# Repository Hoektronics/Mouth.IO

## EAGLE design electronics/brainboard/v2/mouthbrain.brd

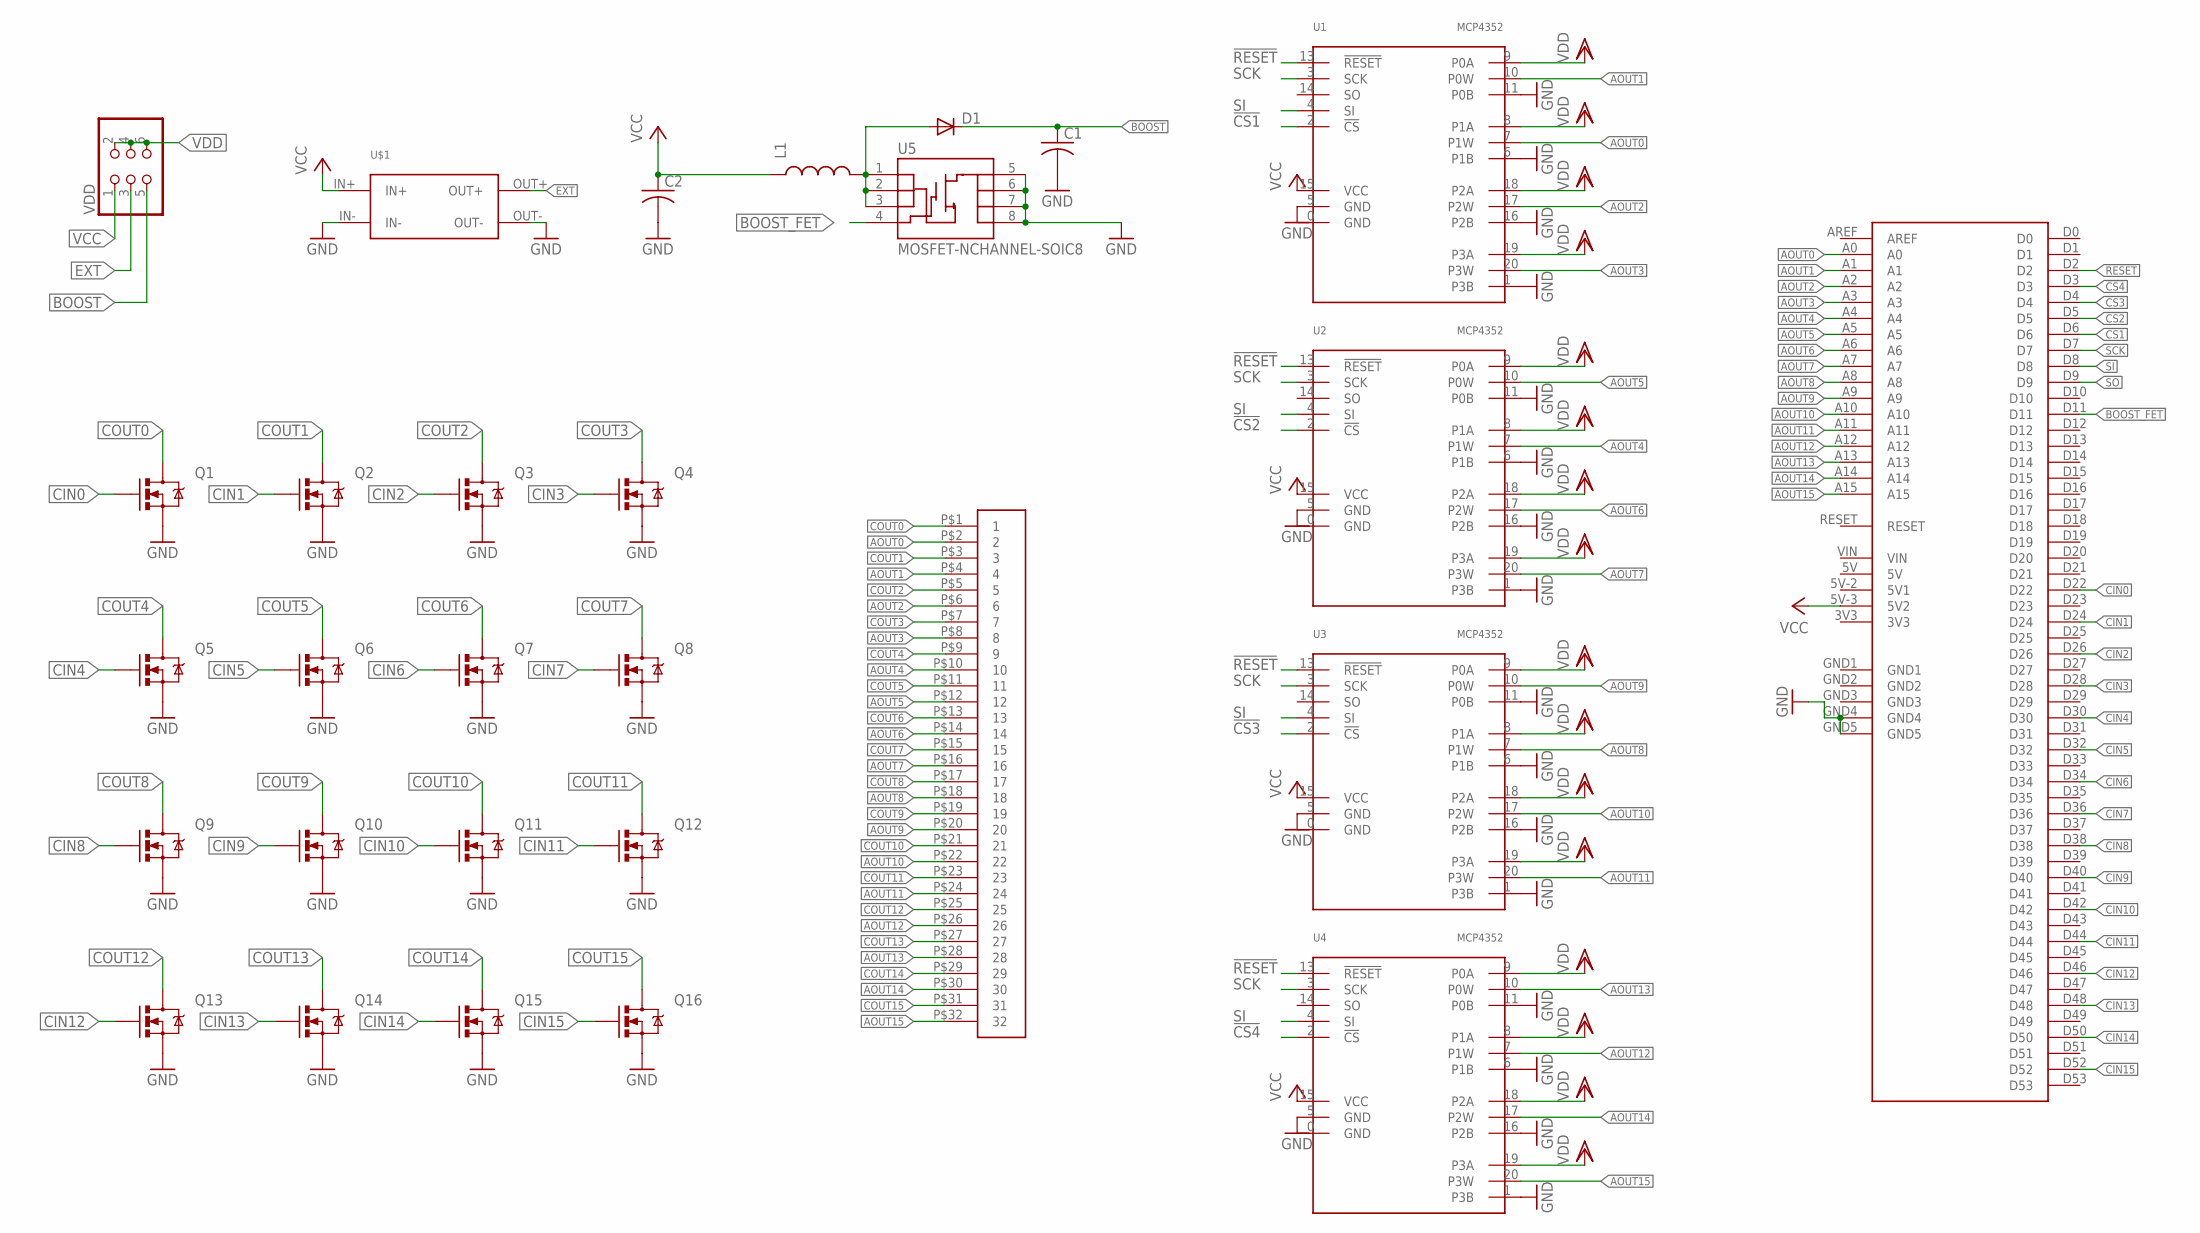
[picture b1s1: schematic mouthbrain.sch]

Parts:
C1, C2: C-USC1206; C1206
D1: DIODESMA; SMA-DIODE
L1: INDUCTOR1206H*; INDUCTOR-1206
Q1, Q2, Q3, Q4, Q5, Q6, Q7, Q8, Q9, Q10, Q11, Q12, Q13, Q14, Q15, Q16: MOSFET-NCHANNELSMD; SOT23-3
U1, U2, U3, U4: MCP4352; QFN-20-PAD
U5: MOSFET-NCHANNEL-SOIC8; SO08
U$1: DC-DC-CONVERTER; DC-DC-MODULE
U$2: FPC-0.5-32HORIZ; FPC-32-HORIZONTAL
U$3: ARDUINO-MEGA
VDD: PINHD-2X3; 2X03

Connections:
!CS1: U1.2 (!CS), U$3.D6
!CS2: U2.2 (!CS), U$3.D5
!CS3: U3.2 (!CS), U$3.D4
!CS4: U4.2 (!CS), U$3.D3
!RESET: U1.13 (!RESET), U2.13 (!RESET), U3.13 (!RESET), U4.13 (!RESET), U$3.D2
AOUT0: U1.7 (P1W), U$2.P$2 (2), U$3.A0
AOUT1: U1.10 (P0W), U$2.P$4 (4), U$3.A1
AOUT2: U1.17 (P2W), U$2.P$6 (6), U$3.A2
AOUT3: U1.20 (P3W), U$2.P$8 (8), U$3.A3
AOUT4: U2.7 (P1W), U$2.P$10 (10), U$3.A4
AOUT5: U2.10 (P0W), U$2.P$12 (12), U$3.A5
AOUT6: U2.17 (P2W), U$2.P$14 (14), U$3.A6
AOUT7: U2.20 (P3W), U$2.P$16 (16), U$3.A7
AOUT8: U3.7 (P1W), U$2.P$18 (18), U$3.A8
AOUT9: U3.10 (P0W), U$2.P$20 (20), U$3.A9
AOUT10: U3.17 (P2W), U$2.P$22 (22), U$3.A10
AOUT11: U3.20 (P3W), U$2.P$24 (24), U$3.A11
AOUT12: U4.7 (P1W), U$2.P$26 (26), U$3.A12
AOUT13: U4.10 (P0W), U$2.P$28 (28), U$3.A13
AOUT14: U4.17 (P2W), U$2.P$30 (30), U$3.A14
AOUT15: U4.20 (P3W), U$2.P$32 (32), U$3.A15
BOOST: C1.1, D1.C, VDD.5
BOOST_FET: U5.4 (G), U$3.D11
CIN0: Q1.1 (G), U$3.D22
CIN1: Q2.1 (G), U$3.D24
CIN2: Q3.1 (G), U$3.D26
CIN3: Q4.1 (G), U$3.D28
CIN4: Q5.1 (G), U$3.D30
CIN5: Q6.1 (G), U$3.D32
CIN6: Q7.1 (G), U$3.D34
CIN7: Q8.1 (G), U$3.D36
CIN8: Q9.1 (G), U$3.D38
CIN9: Q10.1 (G), U$3.D40
CIN10: Q11.1 (G), U$3.D42
CIN11: Q12.1 (G), U$3.D44
CIN12: Q13.1 (G), U$3.D46
CIN13: Q14.1 (G), U$3.D48
CIN14: Q15.1 (G), U$3.D50
CIN15: Q16.1 (G), U$3.D52
COUT0: Q1.3 (D), U$2.P$1 (1)
COUT1: Q2.3 (D), U$2.P$3 (3)
COUT2: Q3.3 (D), U$2.P$5 (5)
COUT3: Q4.3 (D), U$2.P$7 (7)
COUT4: Q5.3 (D), U$2.P$9 (9)
COUT5: Q6.3 (D), U$2.P$11 (11)
COUT6: Q7.3 (D), U$2.P$13 (13)
COUT7: Q8.3 (D), U$2.P$15 (15)
COUT8: Q9.3 (D), U$2.P$17 (17)
COUT9: Q10.3 (D), U$2.P$19 (19)
COUT10: Q11.3 (D), U$2.P$21 (21)
COUT11: Q12.3 (D), U$2.P$23 (23)
COUT12: Q13.3 (D), U$2.P$25 (25)
COUT13: Q14.3 (D), U$2.P$27 (27)
COUT14: Q15.3 (D), U$2.P$29 (29)
COUT15: Q16.3 (D), U$2.P$31 (31)
EXT: U$1.OUT+, VDD.3
GND: C1.2, C2.2, Q1.2 (S), Q2.2 (S), Q3.2 (S), Q4.2 (S), Q5.2 (S), Q6.2 (S), Q7.2 (S), Q8.2 (S), Q9.2 (S), Q10.2 (S), Q11.2 (S), Q12.2 (S), Q13.2 (S), Q14.2 (S), Q15.2 (S), Q16.2 (S), U1.0 (GND), U1.1 (P3B), U1.5 (GND), U1.6 (P1B), U1.11 (P0B), U1.16 (P2B), U2.0 (GND), U2.1 (P3B), U2.5 (GND), U2.6 (P1B), U2.11 (P0B), U2.16 (P2B), U3.0 (GND), U3.1 (P3B), U3.5 (GND), U3.6 (P1B), U3.11 (P0B), U3.16 (P2B), U4.0 (GND), U4.1 (P3B), U4.5 (GND), U4.6 (P1B), U4.11 (P0B), U4.16 (P2B), U5.5 (D), U5.6 (D), U5.7 (D), U5.8 (D), U$1.IN-, U$1.OUT-, U$3.GND4, U$3.GND5
unnamed: D1.A, L1.P$2 (2), U5.1 (S), U5.2 (S), U5.3 (S)
SCK: U1.3 (SCK), U2.3 (SCK), U3.3 (SCK), U4.3 (SCK), U$3.D7
SI: U1.4 (SI), U2.4 (SI), U3.4 (SI), U4.4 (SI), U$3.D8
SO: U$3.D9
VCC: C2.1, L1.P$1 (1), U1.15 (VCC), U2.15 (VCC), U3.15 (VCC), U4.15 (VCC), U$1.IN+, U$3.5V-3 (5V2), VDD.1
VDD: U1.8 (P1A), U1.9 (P0A), U1.18 (P2A), U1.19 (P3A), U2.8 (P1A), U2.9 (P0A), U2.18 (P2A), U2.19 (P3A), U3.8 (P1A), U3.9 (P0A), U3.18 (P2A), U3.19 (P3A), U4.8 (P1A), U4.9 (P0A), U4.18 (P2A), U4.19 (P3A), VDD.2, VDD.4, VDD.6

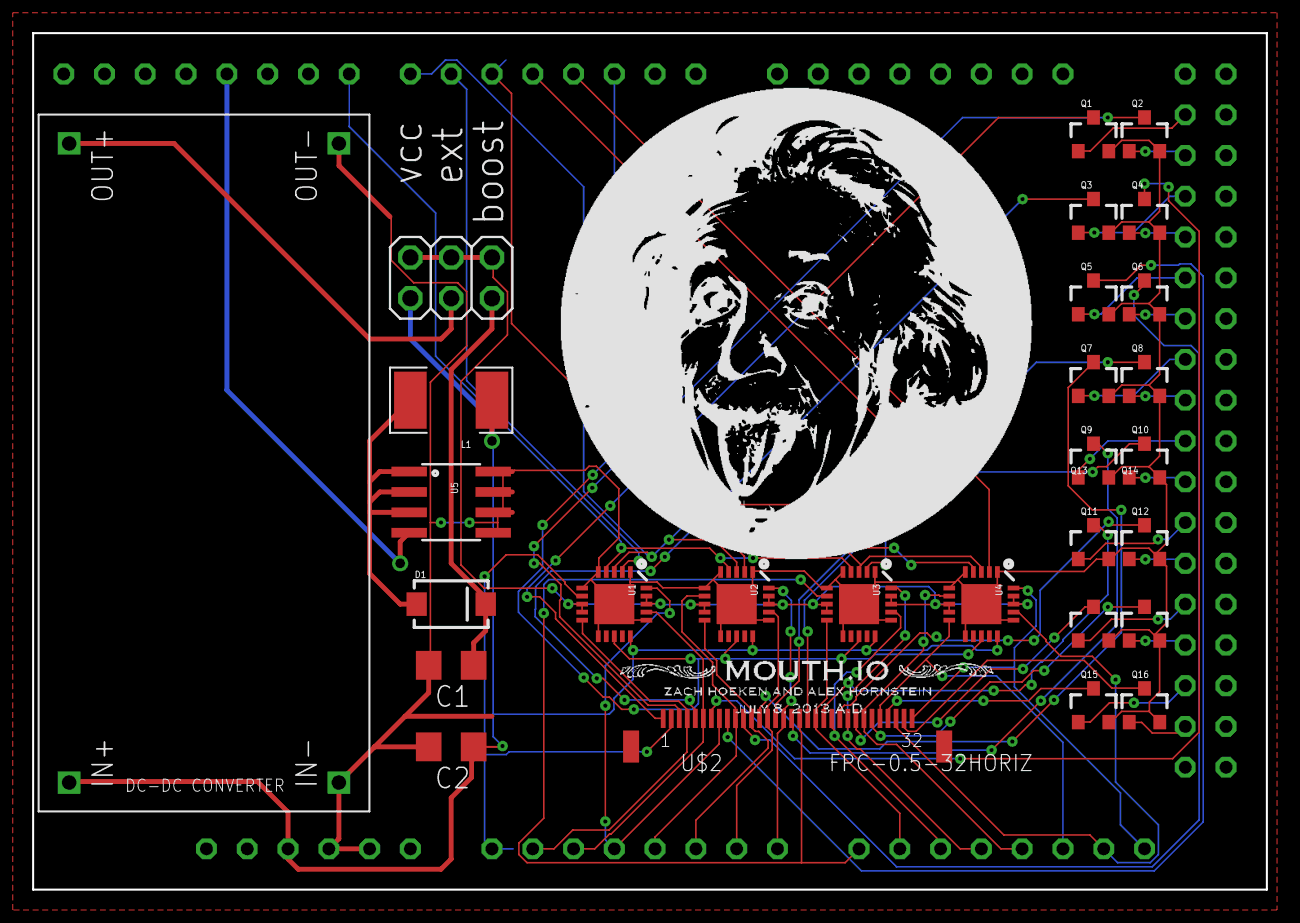
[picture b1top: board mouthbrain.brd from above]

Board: 2 copper layers, 76.8 x 53.3 mm, 29 parts (0 on the bottom side), 62 nets.

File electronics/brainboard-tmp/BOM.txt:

Partlist

Exported from mouthbrain.brd at 8/7/13 3:34 PM

EAGLE Version 6.4.1 Copyright (c) 1988-2013 CadSoft

Assembly variant: 

Part     Value                 Package       Library     Position (mil)        Orientation

C1                             C1206         rcl         (3050 1700)           R270
C2                             C1206         rcl         (3250 1700)           R270
D1                             SMA-DIODE     SparkFun    (2900 1700)           R90
L1                             INDUCTOR-1206 SparkFun    (2400 1700)           R270
MEGA     ARDUINO-MEGAFULL      ARDUINO_MEGA  SparkFun    (0 100)               R0
Q1       MOSFET-NCHANNELSMD    SOT23-3       SparkFun    (2350 900)            R90
Q2       MOSFET-NCHANNELSMD    SOT23-3       SparkFun    (2350 1050)           R90
Q3       MOSFET-NCHANNELSMD    SOT23-3       SparkFun    (2350 1200)           R90
Q4       MOSFET-NCHANNELSMD    SOT23-3       SparkFun    (2350 1350)           R90
Q5       MOSFET-NCHANNELSMD    SOT23-3       SparkFun    (2500 900)            R90
Q6       MOSFET-NCHANNELSMD    SOT23-3       SparkFun    (2500 1050)           R90
Q7       MOSFET-NCHANNELSMD    SOT23-3       SparkFun    (2500 1200)           R90
Q8       MOSFET-NCHANNELSMD    SOT23-3       SparkFun    (2500 1350)           R90
Q9       MOSFET-NCHANNELSMD    SOT23-3       SparkFun    (2650 900)            R90
Q10      MOSFET-NCHANNELSMD    SOT23-3       SparkFun    (2650 1050)           R90
Q11      MOSFET-NCHANNELSMD    SOT23-3       SparkFun    (2650 1200)           R90
Q12      MOSFET-NCHANNELSMD    SOT23-3       SparkFun    (2650 1350)           R90
Q13      MOSFET-NCHANNELSMD    SOT23-3       SparkFun    (2800 900)            R90
Q14      MOSFET-NCHANNELSMD    SOT23-3       SparkFun    (2800 1050)           R90
Q15      MOSFET-NCHANNELSMD    SOT23-3       SparkFun    (2800 1200)           R90
Q16      MOSFET-NCHANNELSMD    SOT23-3       SparkFun    (2800 1350)           R90
U$1      DC-DC-CONVERTER       DC-DC-MODULE  Hoektronics (1294 1146)           R90
U$2      FPC-0.5-32            FPC-PCB-32    Hoektronics (2750 675)            R0
U1       MCP4352               QFN-20        mouthbrain  (3000 1000)           R90
U2       MCP4352               QFN-20        mouthbrain  (3000 1350)           R90
U3       MCP4352               QFN-20        mouthbrain  (3250 1000)           R90
U4       MCP4352               QFN-20        mouthbrain  (3250 1350)           R90
U5       MOSFET-NCHANNEL-SOIC8 SO08          SparkFun    (2650 1700)           R0
VDD                            2X03          pinhead     (2100 1700)           R90

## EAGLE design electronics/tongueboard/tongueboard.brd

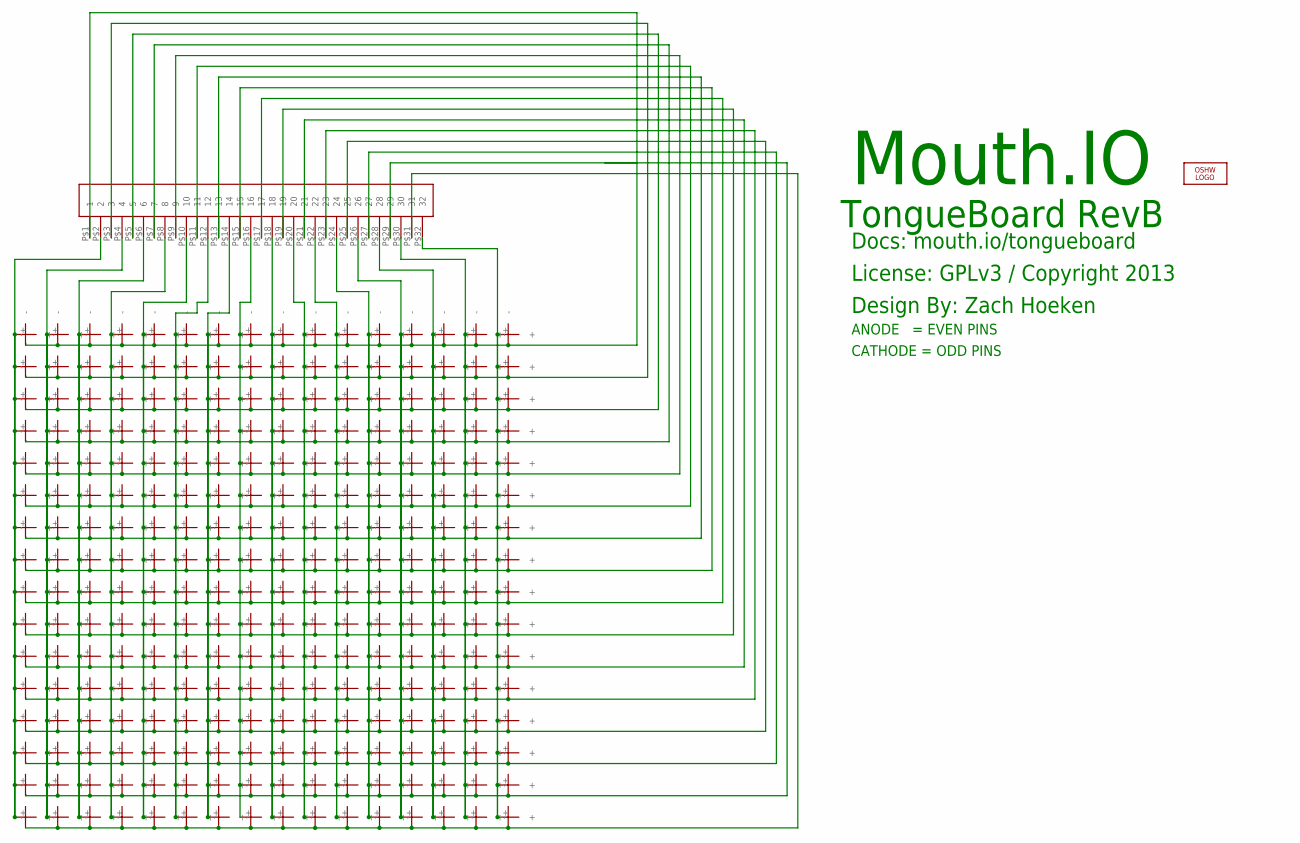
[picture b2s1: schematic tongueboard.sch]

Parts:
LOGO1: OSHW_LOGO_10MIL; OSHW_10X500_NOTEXT_COPPER
U$1, U$2, U$3, U$4, U$5, U$6, U$7, U$8, U$9, U$10, U$11, U$12, U$13, U$14, U$15, U$17, U$18, U$19, U$20, U$21, U$22, U$23, U$24, U$25, U$26, U$27, U$28, U$29, U$30, U$32, U$33, U$34, U$35, U$36, U$37, U$38, U$39, U$40, U$41, U$42, U$43, U$44, U$45, U$47, U$48, U$49, U$50, U$51, U$52, U$53, U$54, U$55, U$56, U$57, U$58, U$59, U$60, U$62, U$63, U$64, U$65, U$66, U$67, U$68, U$69, U$70, U$71, U$72, U$73, U$74, U$75, U$77, U$78, U$79, U$80, U$81, U$82, U$83, U$84, U$85, U$86, U$87, U$88, U$89, U$90, U$92, U$93, U$94, U$95, U$96, U$97, U$98, U$99, U$100, U$101, U$102, U$103, U$104, U$105, U$107, U$108, U$109, U$110, U$111, U$112, U$113, U$114, U$115, U$116, U$117, U$118, U$119, U$120, U$122, U$123, U$124, U$125, U$126, U$127, U$128, U$129, U$130, U$131, U$132, U$133, U$134, U$135, U$137, U$138, U$139, U$140, U$141, U$142, U$143, U$144, U$145, U$146, U$147, U$148, U$149, U$150, U$152, U$153, U$154, U$155, U$156, U$157, U$158, U$159, U$160, U$161, U$162, U$163, U$164, U$165, U$167, U$168, U$169, U$170, U$171, U$172, U$173, U$174, U$175, U$176, U$177, U$178, U$179, U$180, U$182, U$183, U$184, U$185, U$186, U$187, U$188, U$189, U$190, U$191, U$192, U$193, U$194, U$195, U$197, U$198, U$199, U$200, U$201, U$202, U$203, U$204, U$205, U$206, U$207, U$208, U$209, U$210, U$212, U$213, U$214, U$215, U$216, U$217, U$218, U$219, U$220, U$221, U$222, U$223, U$224, U$225, U$227, U$228, U$229, U$230, U$231, U$232, U$233, U$234, U$235, U$236, U$237, U$238, U$239, U$240, U$242, U$243, U$244, U$245, U$246, U$247, U$248, U$249, U$250, U$251, U$252, U$253, U$254, U$255, U$256: ELECTRODE60MIL; 61MIL
U$16, U$31, U$46, U$61, U$76, U$91, U$106, U$121, U$136, U$151, U$166, U$181, U$196, U$211, U$226, U$241: ELECTRODE61MILJCT; 61MILJCT
U$257: FPC-0.5-32; FPC-32-WIRE

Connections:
A0: U$1.+, U$17.+, U$33.+, U$49.+, U$65.+, U$81.+, U$97.+, U$113.+, U$129.+, U$145.+, U$161.+, U$177.+, U$193.+, U$209.+, U$225.+, U$241.+, U$257.P$2 (2)
A1: U$2.+, U$18.+, U$34.+, U$50.+, U$66.+, U$82.+, U$98.+, U$114.+, U$130.+, U$146.+, U$162.+, U$178.+, U$194.+, U$210.+, U$226.+, U$242.+, U$257.P$4 (4)
A2: U$3.+, U$19.+, U$35.+, U$51.+, U$67.+, U$83.+, U$99.+, U$115.+, U$131.+, U$147.+, U$163.+, U$179.+, U$195.+, U$211.+, U$227.+, U$243.+, U$257.P$6 (6)
A3: U$4.+, U$20.+, U$36.+, U$52.+, U$68.+, U$84.+, U$100.+, U$116.+, U$132.+, U$148.+, U$164.+, U$180.+, U$196.+, U$212.+, U$228.+, U$244.+, U$257.P$8 (8)
A4: U$5.+, U$21.+, U$37.+, U$53.+, U$69.+, U$85.+, U$101.+, U$117.+, U$133.+, U$149.+, U$165.+, U$181.+, U$197.+, U$213.+, U$229.+, U$245.+, U$257.P$10 (10)
A5: U$6.+, U$22.+, U$38.+, U$54.+, U$70.+, U$86.+, U$102.+, U$118.+, U$134.+, U$150.+, U$166.+, U$182.+, U$198.+, U$214.+, U$230.+, U$246.+, U$257.P$12 (12)
A6: U$7.+, U$23.+, U$39.+, U$55.+, U$71.+, U$87.+, U$103.+, U$119.+, U$135.+, U$151.+, U$167.+, U$183.+, U$199.+, U$215.+, U$231.+, U$247.+, U$257.P$14 (14)
A7: U$8.+, U$24.+, U$40.+, U$56.+, U$72.+, U$88.+, U$104.+, U$120.+, U$136.+, U$152.+, U$168.+, U$184.+, U$200.+, U$216.+, U$232.+, U$248.+, U$257.P$16 (16)
A8: U$9.+, U$25.+, U$41.+, U$57.+, U$73.+, U$89.+, U$105.+, U$121.+, U$137.+, U$153.+, U$169.+, U$185.+, U$201.+, U$217.+, U$233.+, U$249.+, U$257.P$18 (18)
A9: U$10.+, U$26.+, U$42.+, U$58.+, U$74.+, U$90.+, U$106.+, U$122.+, U$138.+, U$154.+, U$170.+, U$186.+, U$202.+, U$218.+, U$234.+, U$250.+, U$257.P$20 (20)
A10: U$11.+, U$27.+, U$43.+, U$59.+, U$75.+, U$91.+, U$107.+, U$123.+, U$139.+, U$155.+, U$171.+, U$187.+, U$203.+, U$219.+, U$235.+, U$251.+, U$257.P$22 (22)
A11: U$12.+, U$28.+, U$44.+, U$60.+, U$76.+, U$92.+, U$108.+, U$124.+, U$140.+, U$156.+, U$172.+, U$188.+, U$204.+, U$220.+, U$236.+, U$252.+, U$257.P$24 (24)
A12: U$13.+, U$29.+, U$45.+, U$61.+, U$77.+, U$93.+, U$109.+, U$125.+, U$141.+, U$157.+, U$173.+, U$189.+, U$205.+, U$221.+, U$237.+, U$253.+, U$257.P$26 (26)
A13: U$14.+, U$30.+, U$46.+, U$62.+, U$78.+, U$94.+, U$110.+, U$126.+, U$142.+, U$158.+, U$174.+, U$190.+, U$206.+, U$222.+, U$238.+, U$254.+, U$257.P$28 (28)
A14: U$15.+, U$31.+, U$47.+, U$63.+, U$79.+, U$95.+, U$111.+, U$127.+, U$143.+, U$159.+, U$175.+, U$191.+, U$207.+, U$223.+, U$239.+, U$255.+, U$257.P$30 (30)
A15: U$16.+, U$32.+, U$48.+, U$64.+, U$80.+, U$96.+, U$112.+, U$128.+, U$144.+, U$160.+, U$176.+, U$192.+, U$208.+, U$224.+, U$240.+, U$256.+, U$257.P$32 (32)
C0: U$241.-, U$242.-, U$243.-, U$244.-, U$245.-, U$246.-, U$247.-, U$248.-, U$249.-, U$250.-, U$251.-, U$252.-, U$253.-, U$254.-, U$255.-, U$256.-, U$257.P$1 (1)
C1: U$225.-, U$226.-, U$227.-, U$228.-, U$229.-, U$230.-, U$231.-, U$232.-, U$233.-, U$234.-, U$235.-, U$236.-, U$237.-, U$238.-, U$239.-, U$240.-, U$257.P$3 (3)
C2: U$209.-, U$210.-, U$211.-, U$212.-, U$213.-, U$214.-, U$215.-, U$216.-, U$217.-, U$218.-, U$219.-, U$220.-, U$221.-, U$222.-, U$223.-, U$224.-, U$257.P$5 (5)
C3: U$193.-, U$194.-, U$195.-, U$196.-, U$197.-, U$198.-, U$199.-, U$200.-, U$201.-, U$202.-, U$203.-, U$204.-, U$205.-, U$206.-, U$207.-, U$208.-, U$257.P$7 (7)
C4: U$177.-, U$178.-, U$179.-, U$180.-, U$181.-, U$182.-, U$183.-, U$184.-, U$185.-, U$186.-, U$187.-, U$188.-, U$189.-, U$190.-, U$191.-, U$192.-, U$257.P$9 (9)
C5: U$161.-, U$162.-, U$163.-, U$164.-, U$165.-, U$166.-, U$167.-, U$168.-, U$169.-, U$170.-, U$171.-, U$172.-, U$173.-, U$174.-, U$175.-, U$176.-, U$257.P$11 (11)
C6: U$145.-, U$146.-, U$147.-, U$148.-, U$149.-, U$150.-, U$151.-, U$152.-, U$153.-, U$154.-, U$155.-, U$156.-, U$157.-, U$158.-, U$159.-, U$160.-, U$257.P$13 (13)
C7: U$129.-, U$130.-, U$131.-, U$132.-, U$133.-, U$134.-, U$135.-, U$136.-, U$137.-, U$138.-, U$139.-, U$140.-, U$141.-, U$142.-, U$143.-, U$144.-, U$257.P$15 (15)
C8: U$113.-, U$114.-, U$115.-, U$116.-, U$117.-, U$118.-, U$119.-, U$120.-, U$121.-, U$122.-, U$123.-, U$124.-, U$125.-, U$126.-, U$127.-, U$128.-, U$257.P$17 (17)
C9: U$97.-, U$98.-, U$99.-, U$100.-, U$101.-, U$102.-, U$103.-, U$104.-, U$105.-, U$106.-, U$107.-, U$108.-, U$109.-, U$110.-, U$111.-, U$112.-, U$257.P$19 (19)
C10: U$81.-, U$82.-, U$83.-, U$84.-, U$85.-, U$86.-, U$87.-, U$88.-, U$89.-, U$90.-, U$91.-, U$92.-, U$93.-, U$94.-, U$95.-, U$96.-, U$257.P$21 (21)
C11: U$65.-, U$66.-, U$67.-, U$68.-, U$69.-, U$70.-, U$71.-, U$72.-, U$73.-, U$74.-, U$75.-, U$76.-, U$77.-, U$78.-, U$79.-, U$80.-, U$257.P$23 (23)
C12: U$49.-, U$50.-, U$51.-, U$52.-, U$53.-, U$54.-, U$55.-, U$56.-, U$57.-, U$58.-, U$59.-, U$60.-, U$61.-, U$62.-, U$63.-, U$64.-, U$257.P$25 (25)
C13: U$33.-, U$34.-, U$35.-, U$36.-, U$37.-, U$38.-, U$39.-, U$40.-, U$41.-, U$42.-, U$43.-, U$44.-, U$45.-, U$46.-, U$47.-, U$48.-, U$257.P$27 (27)
C14: U$17.-, U$18.-, U$19.-, U$20.-, U$21.-, U$22.-, U$23.-, U$24.-, U$25.-, U$26.-, U$27.-, U$28.-, U$29.-, U$30.-, U$31.-, U$32.-, U$257.P$29 (29)
C15: U$1.-, U$2.-, U$3.-, U$4.-, U$5.-, U$6.-, U$7.-, U$8.-, U$9.-, U$10.-, U$11.-, U$12.-, U$13.-, U$14.-, U$15.-, U$16.-, U$257.P$31 (31)

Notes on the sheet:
Mouth.IO
TongueBoard RevB
ANODE = EVEN PINS
CATHODE = ODD PINS
Docs: mouth.io/tongueboard
License: GPLv3 / Copyright 2013
Design By: Zach Hoeken

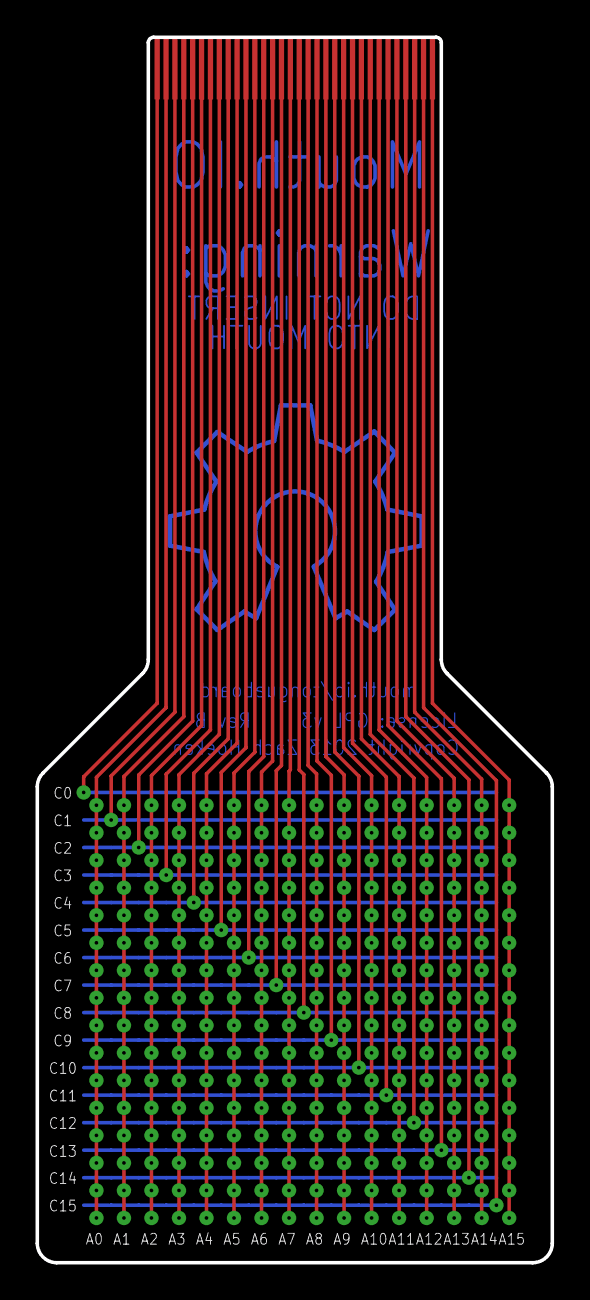
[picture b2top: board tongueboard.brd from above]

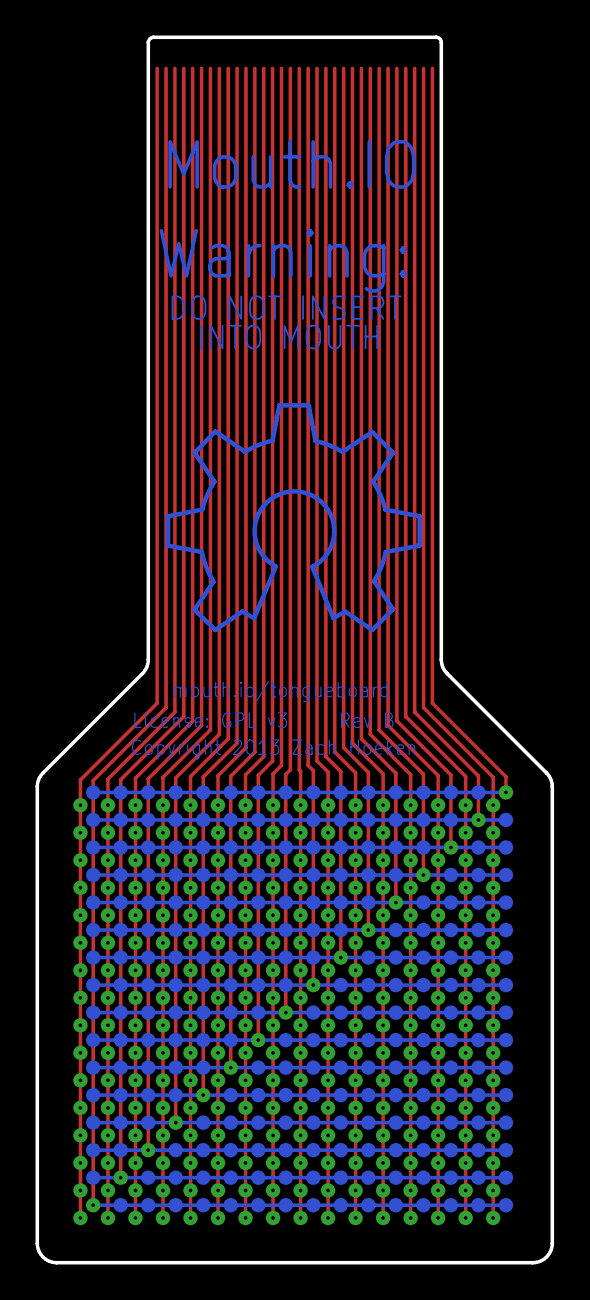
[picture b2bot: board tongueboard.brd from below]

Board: 2 copper layers, 29.0 x 69.0 mm, 258 parts (256 on the bottom side), 32 nets.

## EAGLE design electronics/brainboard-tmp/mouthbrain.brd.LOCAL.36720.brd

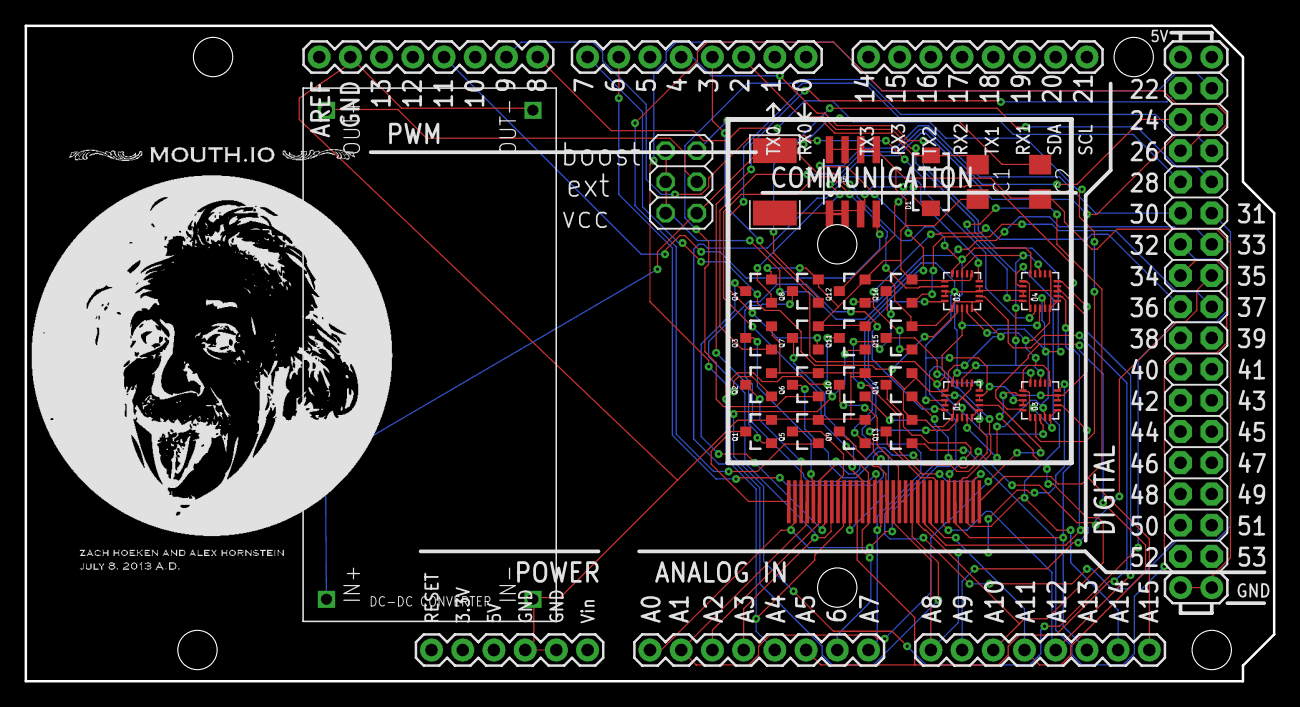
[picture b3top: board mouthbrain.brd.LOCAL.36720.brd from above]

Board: 2 copper layers, 101.6 x 53.3 mm, 29 parts (0 on the bottom side), 62 nets.

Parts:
C1, C2: C1206
D1: SMA-DIODE
L1: INDUCTOR-1206
MEGA: ARDUINO-MEGAFULL; ARDUINO_MEGA
Q1, Q2, Q3, Q4, Q5, Q6, Q7, Q8, Q9, Q10, Q11, Q12, Q13, Q14, Q15, Q16: MOSFET-NCHANNELSMD; SOT23-3
U1, U2, U3, U4: MCP4352; QFN-20
U5: MOSFET-NCHANNEL-SOIC8; SO08
U$1: DC-DC-CONVERTER; DC-DC-MODULE
U$2: FPC-0.5-32; FPC-PCB-32
VDD: 2X03

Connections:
!CS1: MEGA.6, U1.2
!CS2: MEGA.7, U2.2
!CS3: MEGA.8, U3.2
!CS4: MEGA.9, U4.2
!RESET: MEGA.2, U1.13, U2.13, U3.13, U4.13
AOUT0: MEGA.A0, U1.10, U$2.P$2
AOUT1: MEGA.A1, U1.7, U$2.P$4
AOUT2: MEGA.A2, U1.17, U$2.P$6
AOUT3: MEGA.A3, U1.20, U$2.P$8
AOUT4: MEGA.A4, U2.10, U$2.P$10
AOUT5: MEGA.A5, U2.7, U$2.P$12
AOUT6: MEGA.A6, U2.17, U$2.P$14
AOUT7: MEGA.A7, U2.20, U$2.P$16
AOUT8: MEGA.A8, U3.10, U$2.P$18
AOUT9: MEGA.A9, U3.7
AOUT10: MEGA.A10, U3.17, U$2.P$22
AOUT11: MEGA.A11, U3.20, U$2.P$24
AOUT12: MEGA.A12, U4.10, U$2.P$26
AOUT13: MEGA.A13, U4.7, U$2.P$28
AOUT14: MEGA.A14, U4.17, U$2.P$30
AOUT15: MEGA.A15, U4.20, U$2.P$32
BOOST: C1.1, D1.C, VDD.5
BOOST_FET: MEGA.11, U5.4
CIN0: MEGA.22, Q1.1
CIN1: MEGA.23, Q2.1
CIN2: MEGA.24, Q3.1
CIN3: MEGA.25, Q4.1
CIN4: MEGA.26, Q5.1
CIN5: MEGA.27, Q6.1
CIN6: MEGA.28, Q7.1
CIN7: MEGA.29, Q8.1
CIN8: MEGA.30, Q9.1
CIN9: MEGA.31, Q10.1
CIN10: MEGA.32, Q11.1
CIN11: MEGA.33, Q12.1
CIN12: MEGA.34, Q13.1
CIN13: MEGA.35, Q14.1
CIN14: MEGA.36, Q15.1
CIN15: MEGA.37, Q16.1
COUT0: Q1.3, U$2.P$1
COUT1: Q2.3, U$2.P$3
COUT2: Q3.3, U$2.P$5
COUT3: Q4.3, U$2.P$7
COUT4: Q5.3, U$2.P$9
COUT5: Q6.3, U$2.P$11
COUT6: Q7.3, U$2.P$13
COUT7: Q8.3, U$2.P$15
COUT8: Q9.3, U$2.P$17
COUT9: Q10.3, U$2.P$19, U$2.P$20
COUT10: Q11.3, U$2.P$21
COUT11: Q12.3, U$2.P$23
COUT12: Q13.3, U$2.P$25
COUT13: Q14.3, U$2.P$27
COUT14: Q15.3, U$2.P$29
COUT15: Q16.3, U$2.P$31
EXT: U$1.OUT+, VDD.3
GND: C1.2, C2.2, MEGA.GND@0, MEGA.GND@1, MEGA.GND@2, MEGA.GND@3, MEGA.GND@4, Q1.2, Q2.2, Q3.2, Q4.2, Q5.2, Q6.2, Q7.2, Q8.2, Q9.2, Q10.2, Q11.2, Q12.2, Q13.2, Q14.2, Q15.2, Q16.2, U1.1, U1.5, U1.6, U1.11, U1.16, U2.1, U2.5, U2.6, U2.11, U2.16, U3.1, U3.5, U3.6, U3.11, U3.16, U4.1, U4.5, U4.6, U4.11, U4.16, U5.5, U5.6, U5.7, U5.8, U$1.IN-, U$1.OUT-
unnamed: D1.A, L1.P$2, U5.1, U5.2, U5.3
SCK: MEGA.3, U1.3, U2.3, U3.3, U4.3
SI: MEGA.4, U1.4, U2.4, U3.4, U4.4
VCC: C2.1, L1.P$1, U1.15, U2.15, U3.15, U4.15, U$1.IN+, VDD.1
VDD: U1.8, U1.9, U1.18, U1.19, U2.8, U2.9, U2.18, U2.19, U3.8, U3.9, U3.18, U3.19, U4.8, U4.9, U4.18, U4.19, VDD.2, VDD.4, VDD.6

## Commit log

2012-05-10 overhauled the mouthbrain + brainboard designs. still need to route the brainboard.
2012-05-11 started laying out the brainboard with the new circuit.
2012-05-11 finished the first pass layout of the new board.
2012-06-18 tidied up the brainboard for revB release
2012-06-18 removed old irrelevant files.
2012-06-18 renamed mouthbrain to tongboard.
2012-06-21 finished the silkscreen on the tongueboard
2012-06-21 added eagle packaging scripts.
2012-08-19 added urls and frames and such and got ready for a release.
2012-08-19 added release drill and pdf files.
2012-08-19 fixed polygons on brainboard.
2012-08-19 fixed silkscreen errors to prep for prototypes.
2013-07-07 picked back up the project, converted tongueboard to fpc.
2013-07-07 testing commit privs
2013-07-07 added brainboard v2, brainboard with digipots and variable voltage boost converter
2013-07-08 tongueboard ready for release.
2013-07-08 circuit is ready to rock and roll.
2013-07-08 routed the brainboard
2013-07-09 latest routing
2013-07-09 routed a bunch of the brainboard.
2013-07-09 layout mods to the brainboard.
2013-07-09 switched ADCs to package with ground pad
2013-07-11 tweaked the settings for soldermask.
2013-07-16 mouthbrain ready for prototyping.
2013-07-16 added important release docs.
2013-07-16 restructuring #1.
2013-07-16 restructure #2
2013-07-16 fully restructured.
2013-07-22 created an arduino library for Mouthio

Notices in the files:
electronics/tongueboard/tongueboard.brd:
Copyright 2013 Zach Hoeken
License: GPL v3 Rev B
parts and their libraries:
SparkFun: Licensing: CC v3.0 Share-Alike You are welcome to use this library for commercial purposes.
